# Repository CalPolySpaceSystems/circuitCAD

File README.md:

# Circuit CAD
This repository contains Cal Poly Space Systems' circuit board Design files. 
This includes designed PCBs as well as other resources.
See READMEs in each directory for more information.

# Projects
* UpBoard
* CubeStack
* Flight Recorders
* Peripherals
* Breakouts

# Resources
* Component Libraries
* Design Block/Subassembly Libraries
* CAM jobs for exporting Gerber Files of PCBs

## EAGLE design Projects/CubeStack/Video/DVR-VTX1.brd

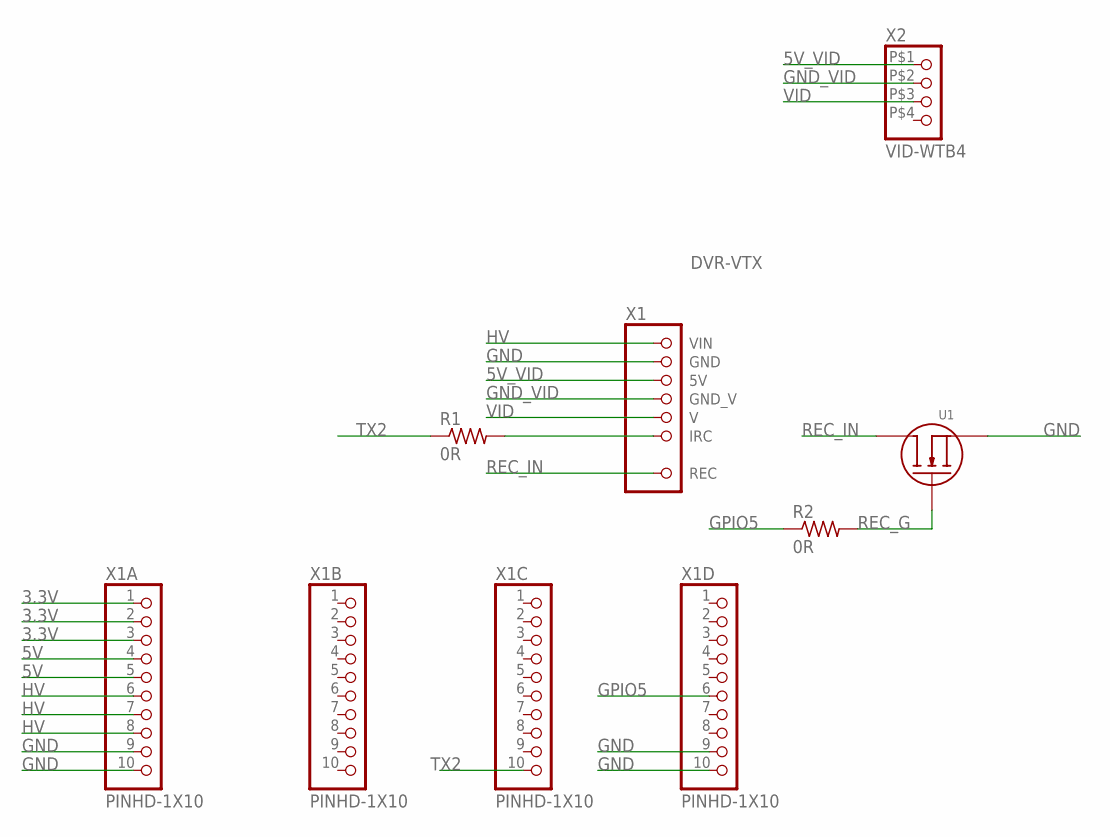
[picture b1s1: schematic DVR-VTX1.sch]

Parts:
R1, R2: 0R; R0603
U1: 2N7002E; NMINI3-R1-B
X1: DVR-VTX
X1A, X1B, X1C, X1D: PINHD-1X10; 1X10-BIG
X2: VID-WTB4; 10114829-10104LF

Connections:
3.3V: X1A.1, X1A.2, X1A.3
5V: X1A.4, X1A.5
5V_VID: X1.P$3 (5V), X2.P$1 (1)
GND: U1.2 (S), X1.P$2 (GND), X1A.9, X1A.10, X1D.9, X1D.10
GND_VID: X1.P$4 (GND_V), X2.P$2 (2)
GPIO5: R2.1, X1D.6
HV: X1.P$1 (VIN), X1A.6, X1A.7, X1A.8
REC_G: R2.2, U1.1 (G)
REC_IN: U1.3 (D), X1.P$7 (REC)
TRAMP: R1.2, X1.P$6 (IRC)
TX2: R1.1, X1C.10
VID: X1.P$5 (V), X2.P$3 (3)

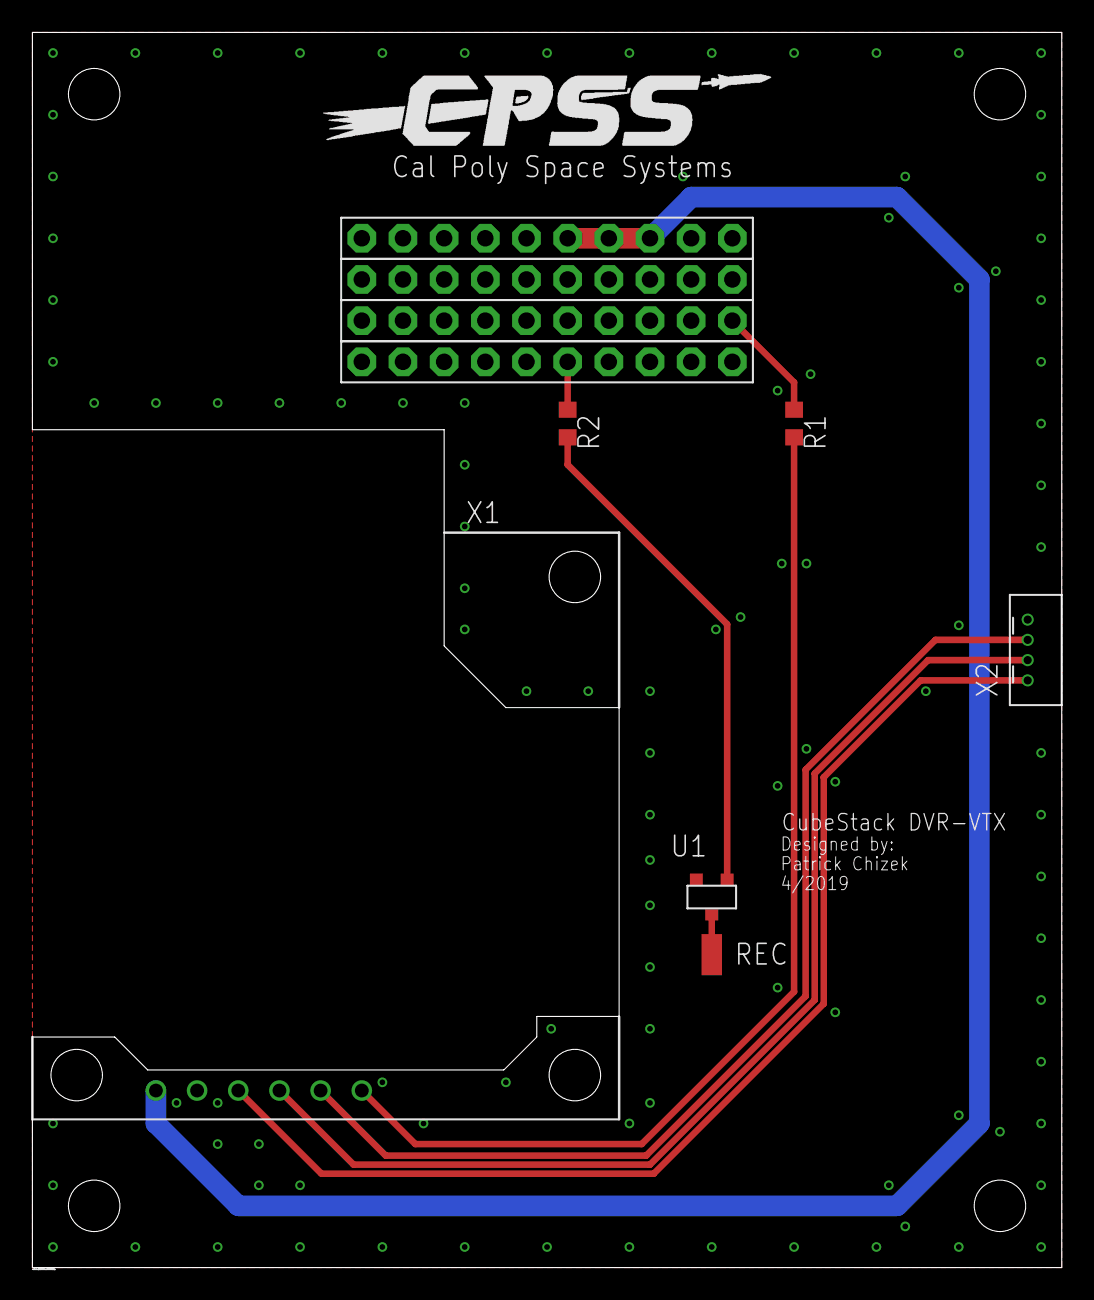
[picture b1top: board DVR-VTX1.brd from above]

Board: 2 copper layers, 63.5 x 76.2 mm, 9 parts (0 on the bottom side), 12 nets.

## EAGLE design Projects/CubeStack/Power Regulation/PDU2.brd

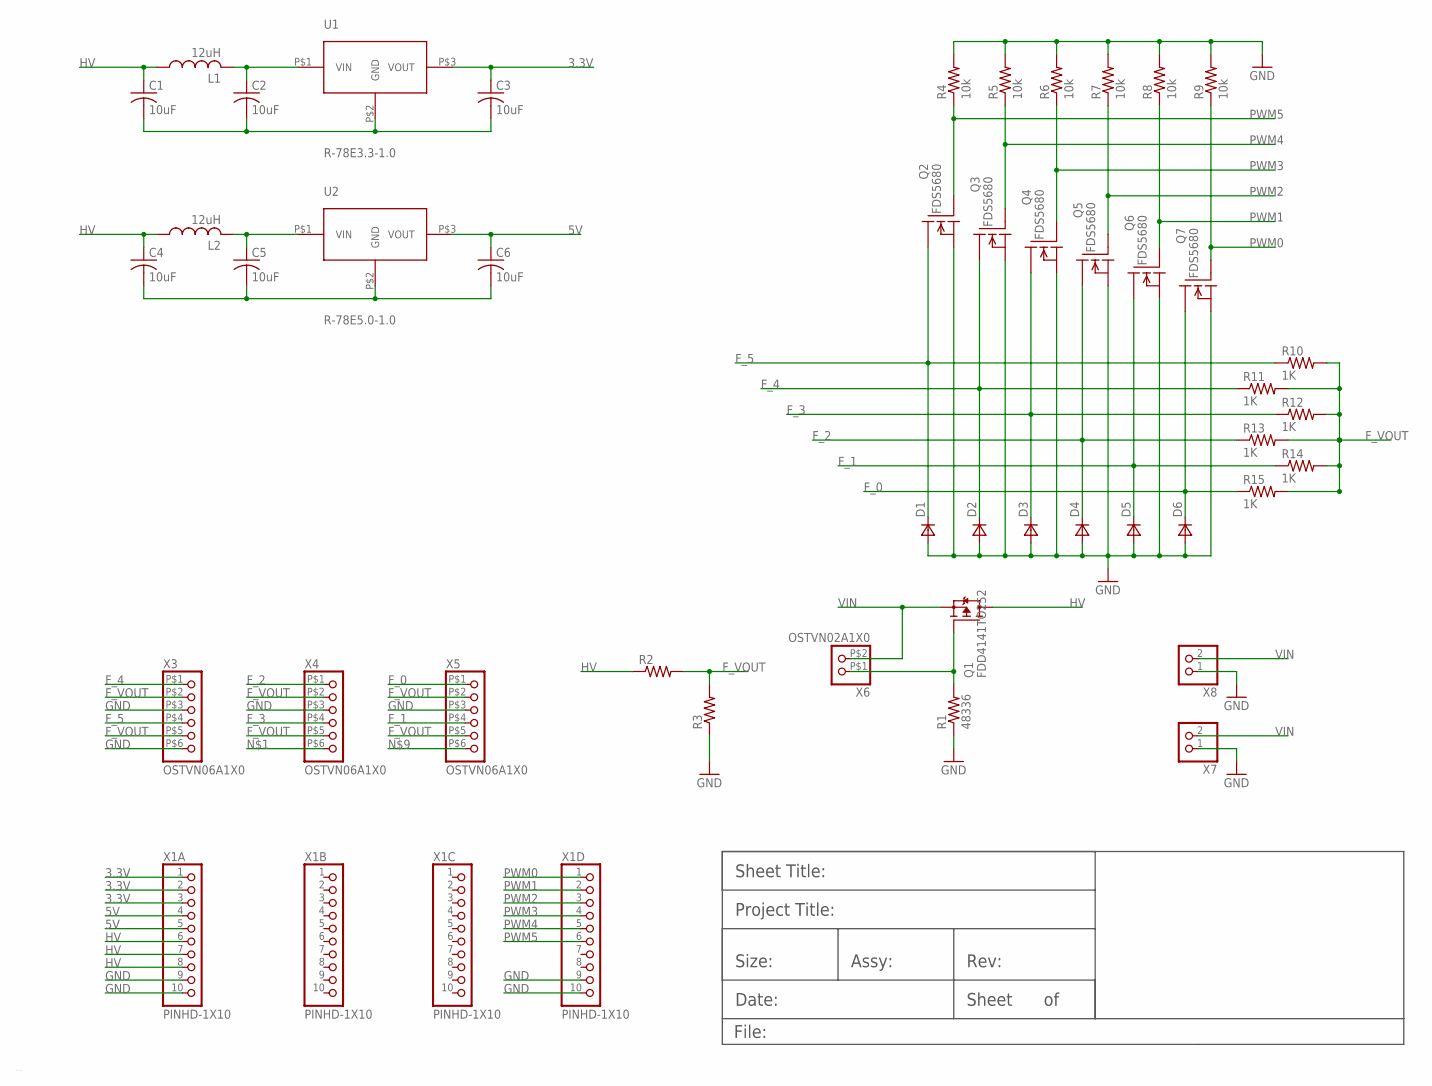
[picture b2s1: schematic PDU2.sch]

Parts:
C1, C2, C3, C4, C5, C6: 10uF; C1206
D1, D2, D3, D4, D5, D6: DSOD323; SOD323
L1, L2: 12uH; L2012C
Q1: FDD4141TO252; TO252
Q2, Q3, Q4, Q5, Q6, Q7: FDS5680; SO-8
R1: 48336; R1206
R2, R3: R-US_R6332; R6332
R4, R5, R6, R7, R8, R9: 10k; R0603
R10, R11, R12, R13, R14, R15: 1K; R0603
U1: R-78E3.3-1.0; R-78E-1.0
U2: R-78E5.0-1.0; R-78E-1.0
X1A, X1B, X1C, X1D: PINHD-1X10; 1X10-BIG
X3, X4, X5: OSTVN06A1X0
X6: OSTVN02A1X0
X7, X8: PINHD-1X2/90; 1X02/90

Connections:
3.3V: C3.1, U1.P$3 (VOUT), X1A.1, X1A.2, X1A.3
5V: C6.1, U2.P$3 (VOUT), X1A.4, X1A.5
EN: Q1.1 (G), R1.2, X6.P$1 (1)
F_0: D6.1 (C), Q7.5 (D), Q7.6 (D), Q7.7 (D), Q7.8 (D), R15.1, X5.P$1 (1)
F_1: D5.1 (C), Q6.5 (D), Q6.6 (D), Q6.7 (D), Q6.8 (D), R14.1, X5.P$4 (4)
F_2: D4.1 (C), Q5.5 (D), Q5.6 (D), Q5.7 (D), Q5.8 (D), R13.1, X4.P$1 (1)
F_3: D3.1 (C), Q4.5 (D), Q4.6 (D), Q4.7 (D), Q4.8 (D), R12.1, X4.P$4 (4)
F_4: D2.1 (C), Q3.5 (D), Q3.6 (D), Q3.7 (D), Q3.8 (D), R11.1, X3.P$1 (1)
F_5: D1.1 (C), Q2.5 (D), Q2.6 (D), Q2.7 (D), Q2.8 (D), R10.1, X3.P$4 (4)
F_VOUT: R2.2, R3.2, R10.2, R11.2, R12.2, R13.2, R14.2, R15.2, X3.P$2 (2), X3.P$5 (5), X4.P$2 (2), X4.P$5 (5), X5.P$2 (2), X5.P$5 (5)
GND: C1.2, C2.2, C3.2, C4.2, C5.2, C6.2, D1.2 (A), D2.2 (A), D3.2 (A), D4.2 (A), D5.2 (A), D6.2 (A), Q2.1 (S), Q2.2 (S), Q2.3 (S), Q3.1 (S), Q3.2 (S), Q3.3 (S), Q4.1 (S), Q4.2 (S), Q4.3 (S), Q5.1 (S), Q5.2 (S), Q5.3 (S), Q6.1 (S), Q6.2 (S), Q6.3 (S), Q7.1 (S), Q7.2 (S), Q7.3 (S), R1.1, R3.1, R4.2, R5.2, R6.2, R7.2, R8.2, R9.2, U1.P$2 (GND), U2.P$2 (GND), X1A.9, X1A.10, X1D.9, X1D.10, X3.P$3 (3), X3.P$6 (6), X4.P$3 (3), X5.P$3 (3), X7.1, X8.1
HV: C1.1, C4.1, L1.1, L2.1, Q1.3 (D), R2.1, X1A.6, X1A.7, X1A.8
unnamed: C2.1, L1.2, U1.P$1 (VIN)
unnamed: C5.1, L2.2, U2.P$1 (VIN)
PWM0: Q7.4 (G), R9.1, X1D.1
PWM1: Q6.4 (G), R8.1, X1D.2
PWM2: Q5.4 (G), R7.1, X1D.3
PWM3: Q4.4 (G), R6.1, X1D.4
PWM4: Q3.4 (G), R5.1, X1D.5
PWM5: Q2.4 (G), R4.1, X1D.6
VIN: Q1.2 (S), X6.P$2 (2), X7.2, X8.2

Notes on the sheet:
C:/Users/patri/Pictures/CPSSLOGO.bmp

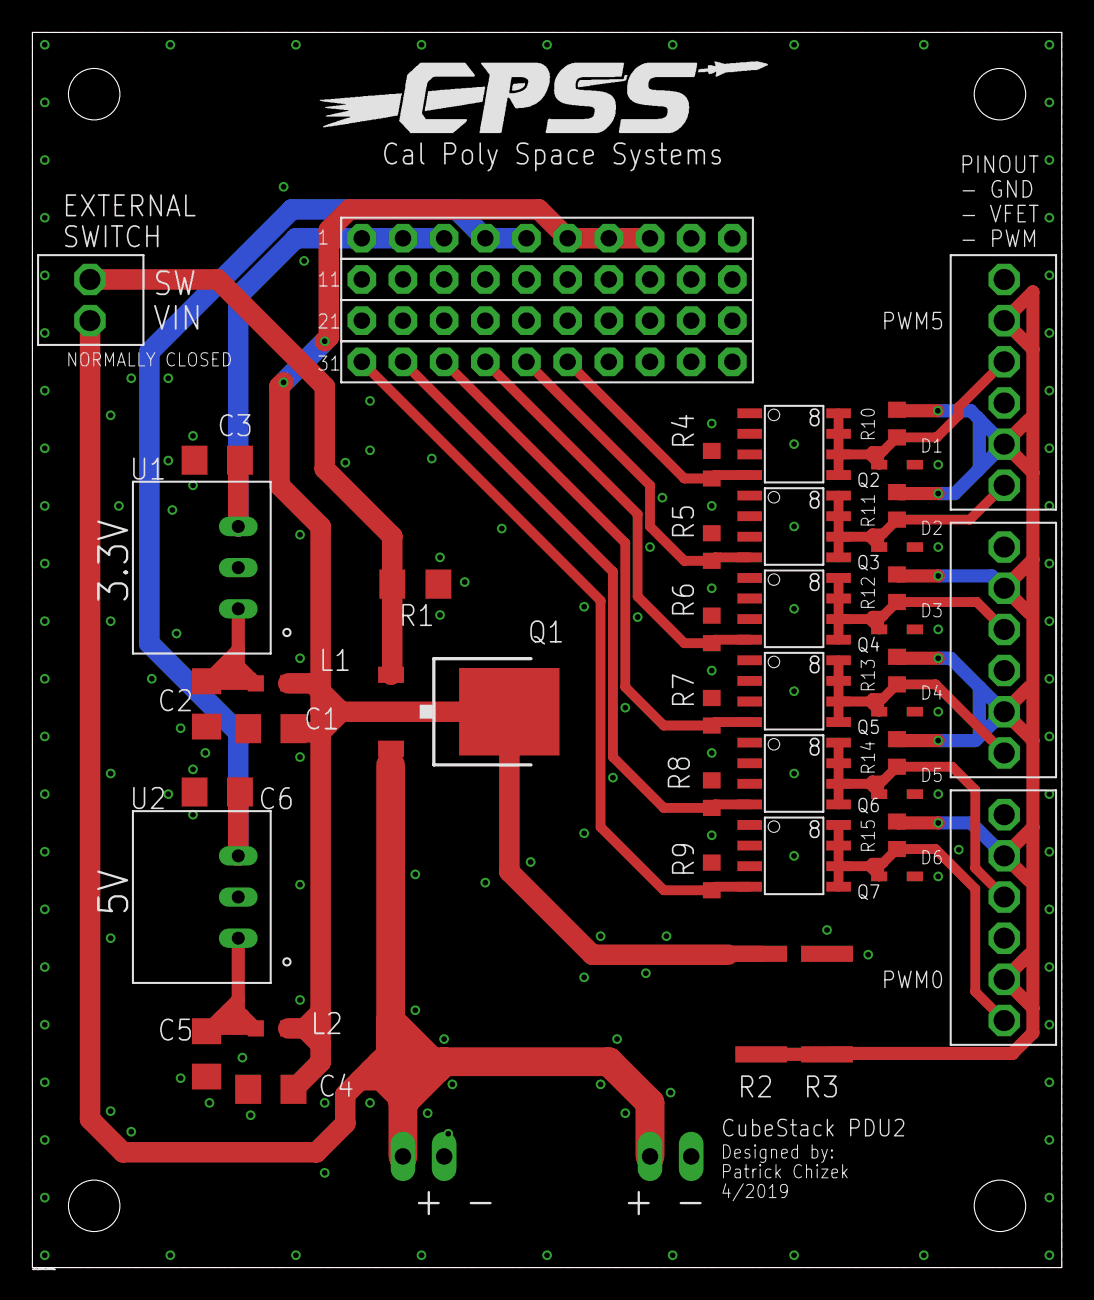
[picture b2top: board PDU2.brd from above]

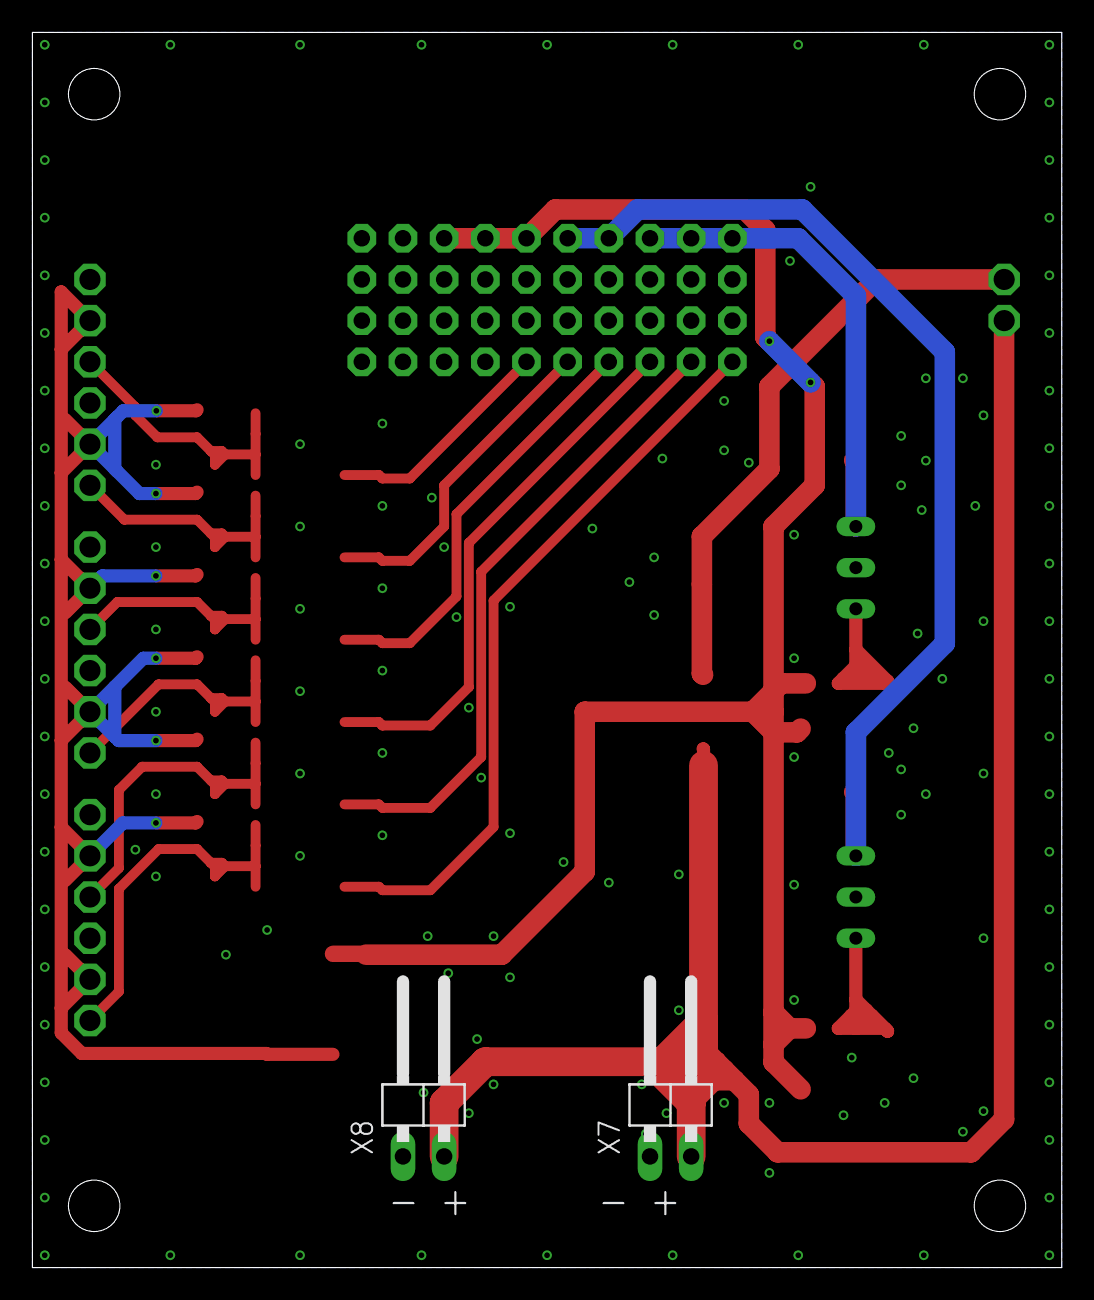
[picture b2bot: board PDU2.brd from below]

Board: 2 copper layers, 63.5 x 76.2 mm, 48 parts (2 on the bottom side), 21 nets.

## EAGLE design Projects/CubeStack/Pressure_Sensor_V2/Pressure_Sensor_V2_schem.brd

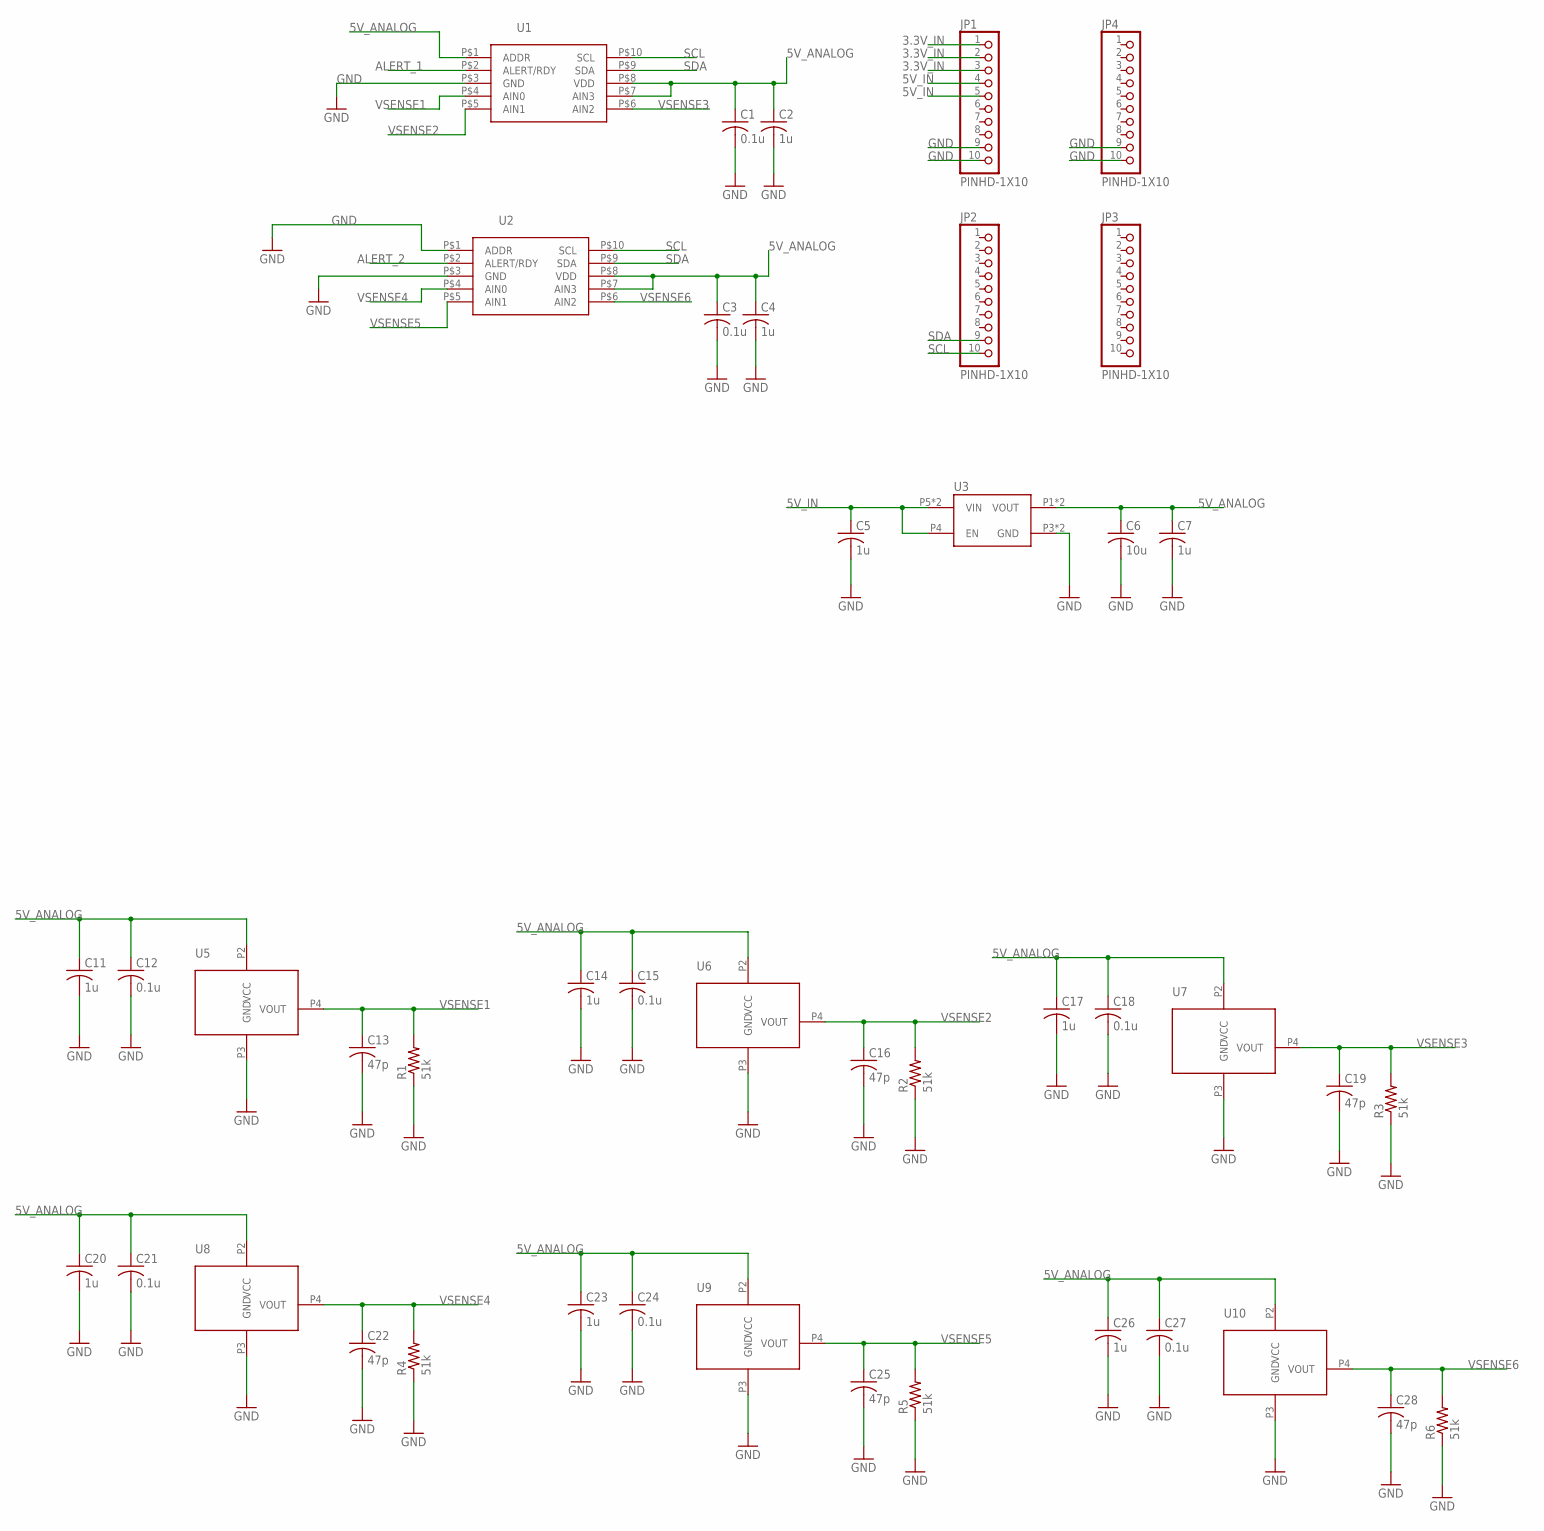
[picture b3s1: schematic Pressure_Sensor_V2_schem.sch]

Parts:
C1, C3, C12, C15, C18, C21, C24, C27: 0.1u; C0805
C2, C4, C5, C7, C11, C14, C17, C20, C23, C26: 1u; C0805
C6: 10u; C0805
C13, C16, C19, C22, C25, C28: 47p; C0805
JP1, JP2, JP3, JP4: PINHD-1X10; 1X10-BIG
R1, R2, R3, R4, R5, R6: 51k; R0805
U1, U2: ADS1115VSSOP; VSSOP-10
U3: ADP196; WLCSP
U5, U6, U7, U8, U9, U10: MPXH6400A; SSOP

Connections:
3.3V_IN: JP1.1, JP1.2, JP1.3
5V_ANALOG: C1.1, C2.1, C3.1, C4.1, C6.1, C7.1, C11.1, C12.1, C14.1, C15.1, C17.1, C18.1, C20.1, C21.1, C23.1, C24.1, C26.1, C27.1, U1.P$1 (ADDR), U1.P$7 (AIN3), U1.P$8 (VDD), U2.P$7 (AIN3), U2.P$8 (VDD), U3.P1 (VOUT), U3.P2 (VOUT), U5.P2 (VCC), U6.P2 (VCC), U7.P2 (VCC), U8.P2 (VCC), U9.P2 (VCC), U10.P2 (VCC)
5V_IN: C5.1, JP1.4, JP1.5, U3.P4 (EN), U3.P5 (VIN), U3.P6 (VIN)
ALERT_1: U1.P$2 (ALERT/RDY)
ALERT_2: U2.P$2 (ALERT/RDY)
GND: C1.2, C2.2, C3.2, C4.2, C5.2, C6.2, C7.2, C11.2, C12.2, C13.2, C14.2, C15.2, C16.2, C17.2, C18.2, C19.2, C20.2, C21.2, C22.2, C23.2, C24.2, C25.2, C26.2, C27.2, C28.2, JP1.9, JP1.10, JP4.9, JP4.10, R1.1, R2.1, R3.1, R4.1, R5.1, R6.1, U1.P$3 (GND), U2.P$1 (ADDR), U2.P$3 (GND), U3.P3 (GND), U3.TH (GND), U5.P3 (GND), U6.P3 (GND), U7.P3 (GND), U8.P3 (GND), U9.P3 (GND), U10.P3 (GND)
SCL: JP2.10, U1.P$10 (SCL), U2.P$10 (SCL)
SDA: JP2.9, U1.P$9 (SDA), U2.P$9 (SDA)
VSENSE1: C13.1, R1.2, U1.P$4 (AIN0), U5.P4 (VOUT)
VSENSE2: C16.1, R2.2, U1.P$5 (AIN1), U6.P4 (VOUT)
VSENSE3: C19.1, R3.2, U1.P$6 (AIN2), U7.P4 (VOUT)
VSENSE4: C22.1, R4.2, U2.P$4 (AIN0), U8.P4 (VOUT)
VSENSE5: C25.1, R5.2, U2.P$5 (AIN1), U9.P4 (VOUT)
VSENSE6: C28.1, R6.2, U2.P$6 (AIN2), U10.P4 (VOUT)

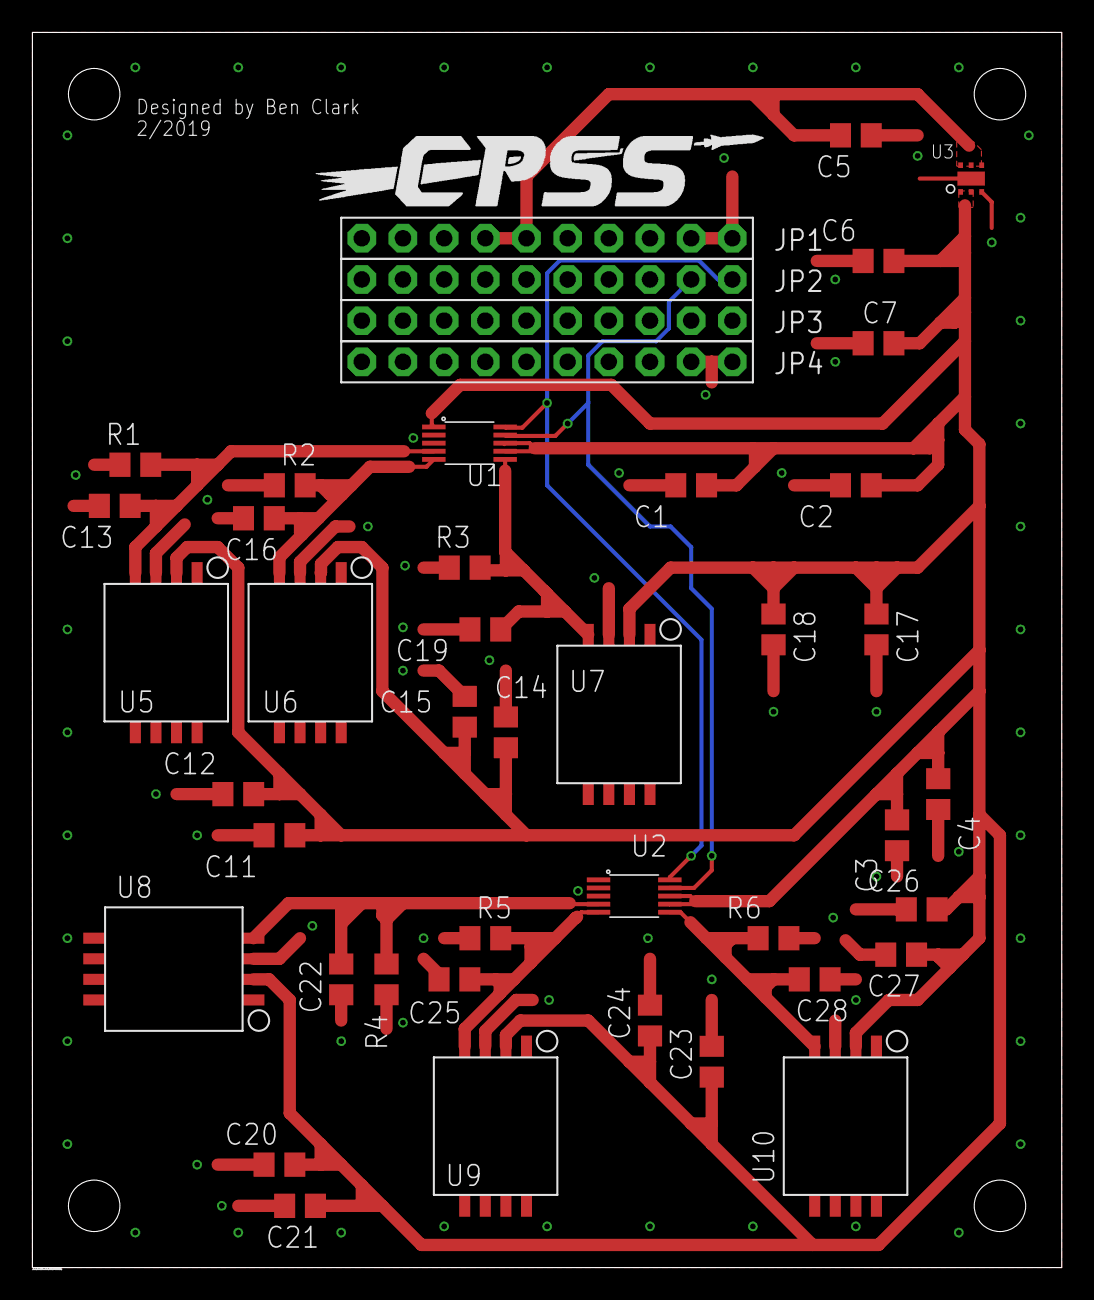
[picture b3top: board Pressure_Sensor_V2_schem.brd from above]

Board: 2 copper layers, 63.5 x 76.2 mm, 44 parts (0 on the bottom side), 12 nets.

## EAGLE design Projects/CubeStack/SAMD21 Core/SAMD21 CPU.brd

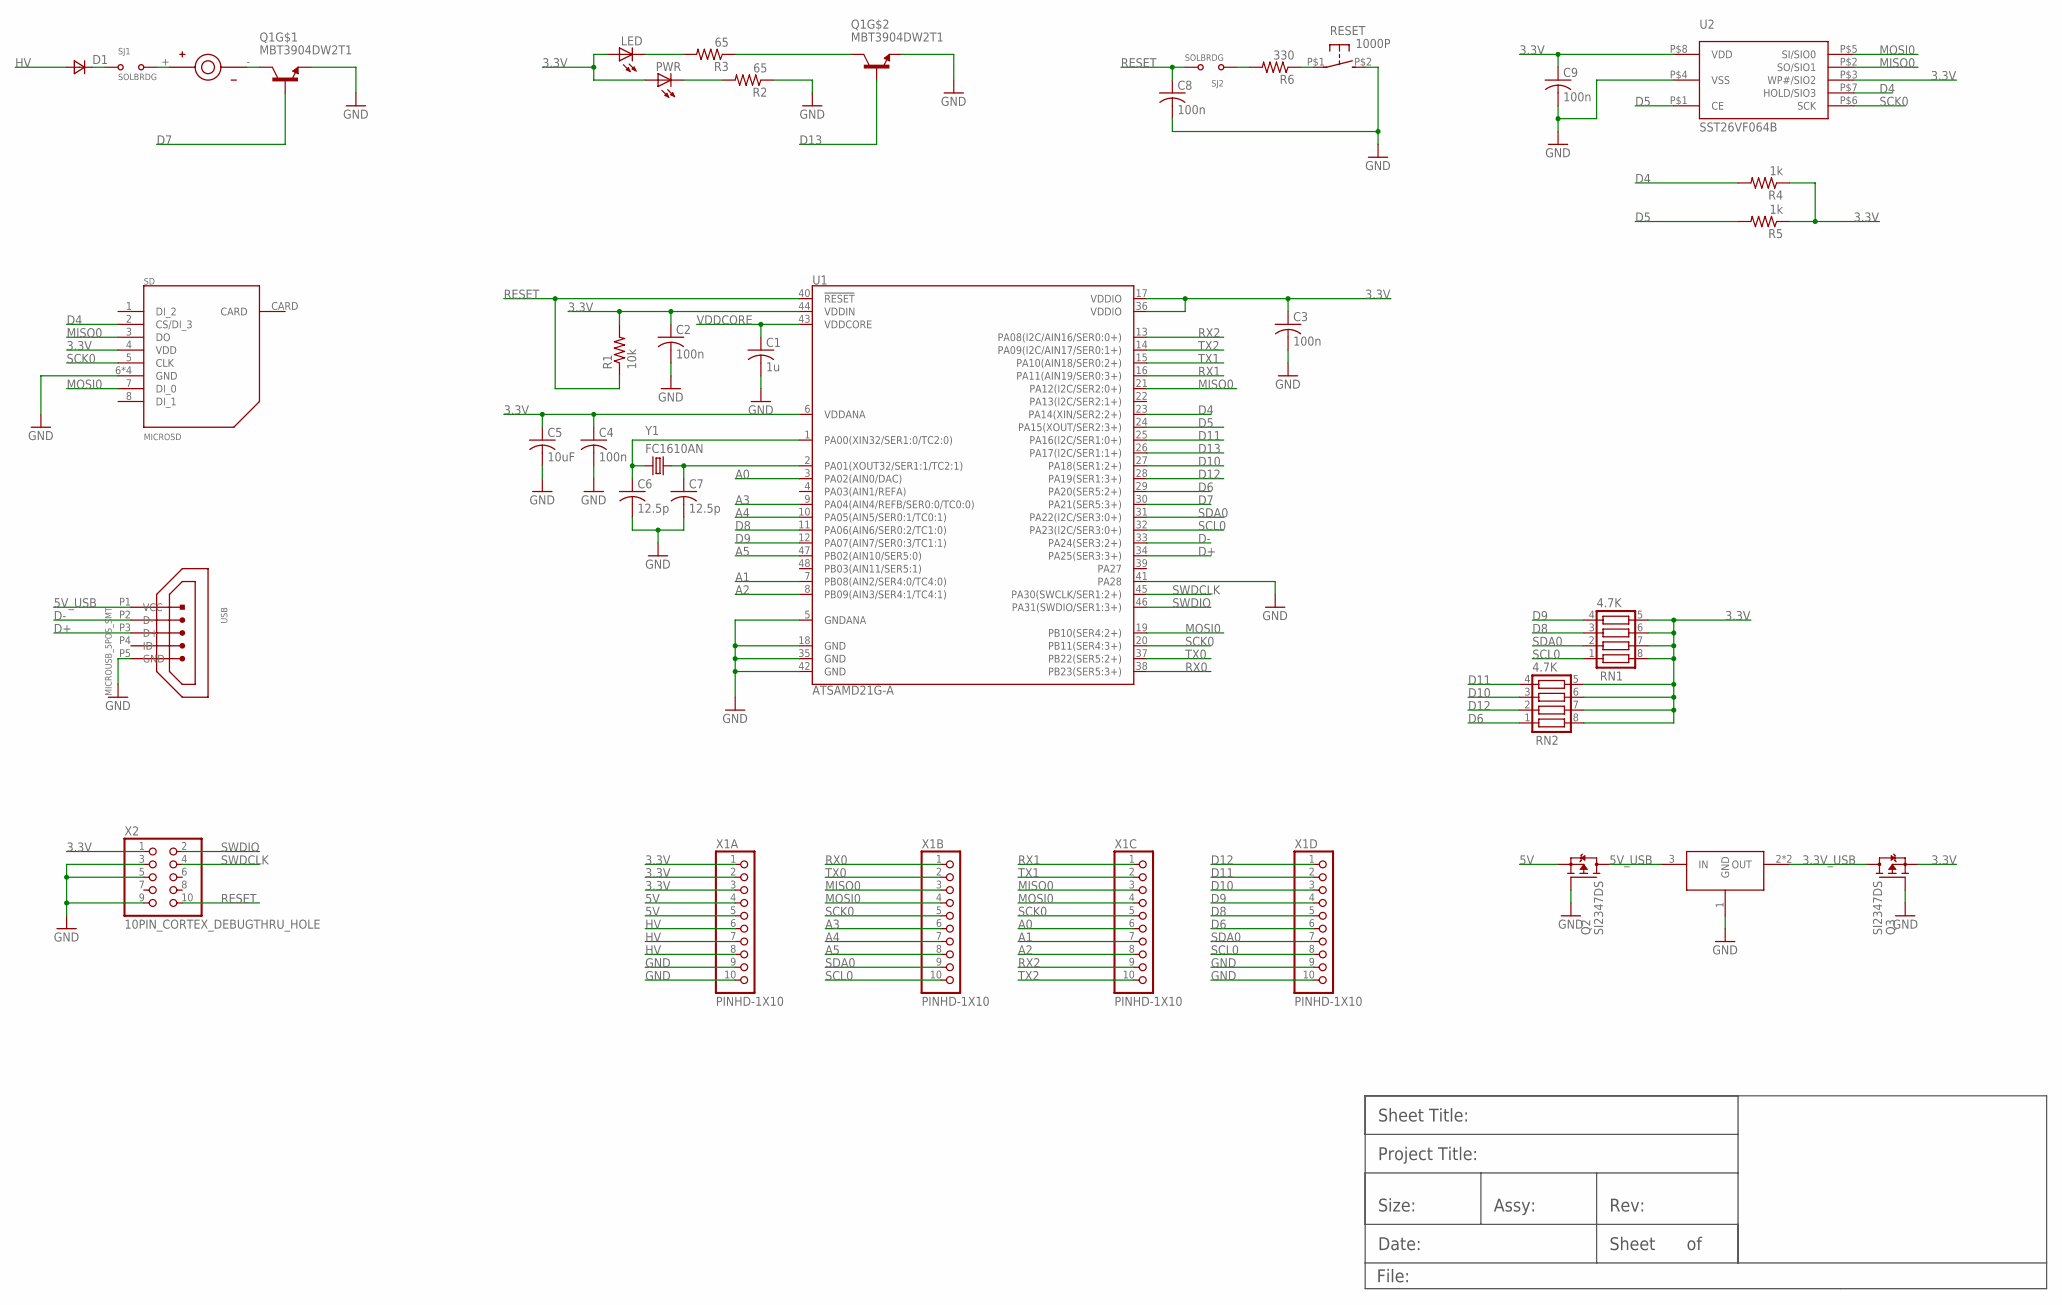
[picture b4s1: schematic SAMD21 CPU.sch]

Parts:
C1: 1u; C0603
C2, C3, C4, C8, C9: 100n; C0603
C5: 10uF; C0603
C6, C7: 12.5p; C0603
D1: DSOD323; SOD323
LED: LEDCHIPLED_0805; CHIPLED_0805
LS1: AI-1440-TWT-24V-2-R; AI-1440-TWT-24-2-R
PWR: LEDCHIPLED_0805; CHIPLED_0805
Q1: MBT3904DW2T1; SOT-363
Q2, Q3: SI2347DS; SOT23
R1: 10k; R0603
R2, R3: 65; R0603
R4, R5: 1k; R0603
R6: 330; R0603
RESET: 1000P; B3U-1000P
RN1, RN2: 4.7K; CTS742C083
SD: MICROSD; CONN_MICROSD
SJ1, SJ2: SOLBRDG
U1: ATSAMD21G-A; TQFP-48
U2: SST26VF064B; SOIJ
U3: AZ1117C; SOT89
USB: MICROUSB_5POS_SMT; RECPT_SMT_R/A
X1A, X1B, X1C, X1D: PINHD-1X10; 1X10-BIG
X2: 10PIN_CORTEX_DEBUGTHRU_HOLE; 2X5-PTH-1.27MM
Y1: FC1610AN; A431L

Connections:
3.3V: C2.1, C3.1, C4.1, C5.1, C9.1, LED.A, PWR.A, Q3.2 (S), R1.2, R4.1, R5.1, RN1.5, RN1.6, RN1.7, RN1.8, RN2.5, RN2.6, RN2.7, RN2.8, SD.4 (VDD), U1.6 (VDDANA), U1.17 (VDDIO), U1.36 (VDDIO), U1.44 (VDDIN), U2.P$3 (WP#/SIO2), U2.P$8 (VDD), X1A.1, X1A.2, X1A.3, X2.1
3.3V_USB: Q3.3 (D), U3.2 (OUT), U3.2@1 (OUT)
5V: Q2.2 (S), X1A.4, X1A.5
5V_USB: Q2.3 (D), U3.3 (IN), USB.P1 (VCC)
A0: U1.3 (PA02(AIN0/DAC)), X1C.6
A1: U1.7 (PB08(AIN2/SER4:0/TC4:0)), X1C.7
A2: U1.8 (PB09(AIN3/SER4:1/TC4:1)), X1C.8
A3: U1.9 (PA04(AIN4/REFB/SER0:0/TC0:0)), X1B.6
A4: U1.10 (PA05(AIN5/SER0:1/TC0:1)), X1B.7
A5: U1.47 (PB02(AIN10/SER5:0)), X1B.8
D4: R4.2, SD.2 (CS/DI_3), U1.23 (PA14(XIN/SER2:2+)), U2.P$7 (HOLD/SIO3)
D5: R5.2, U1.24 (PA15(XOUT/SER2:3+)), U2.P$1 (CE)
D6: RN2.1, U1.29 (PA20(SER5:2+)), X1D.6
D7: Q1.P$2 (B), U1.30 (PA21(SER5:3+))
D8: RN1.3, U1.11 (PA06(AIN6/SER0:2/TC1:0)), X1D.5
D9: RN1.4, U1.12 (PA07(AIN7/SER0:3/TC1:1)), X1D.4
D10: RN2.3, U1.27 (PA18(SER1:2+)), X1D.3
D11: RN2.4, U1.25 (PA16(I2C/SER1:0+)), X1D.2
D12: RN2.2, U1.28 (PA19(SER1:3+)), X1D.1
D13: Q1.P$1 (B), U1.26 (PA17(I2C/SER1:1+))
D+: U1.34 (PA25(SER3:3+)), USB.P3 (D+)
D-: U1.33 (PA24(SER3:2+)), USB.P2 (D-)
GND: C1.2, C2.2, C3.2, C4.2, C5.2, C6.2, C7.2, C8.2, C9.2, Q1.P$3 (E), Q1.P$6 (E), Q2.1 (G), Q3.1 (G), R2.1, RESET.P$2 (S), SD.6 (GND), SD.GND1 (GND), SD.GND2 (GND), SD.GND3 (GND), U1.5 (GNDANA), U1.18 (GND), U1.35 (GND), U1.41 (PA28), U1.42 (GND), U2.P$4 (VSS), U3.1 (GND), USB.P5 (GND), X1A.9, X1A.10, X1D.9, X1D.10, X2.3, X2.5, X2.9
HV: D1.2 (A), X1A.6, X1A.7, X1A.8
LS_D: LS1.-, Q1.P$4 (C)
L_3: LED.C, R3.2
L_3_D: Q1.P$5 (C), R3.1
MISO0: SD.3 (DO), U1.21 (PA12(I2C/SER2:0+)), U2.P$2 (SO/SIO1), X1B.3, X1C.3
MOSI0: SD.7 (DI_0), U1.19 (PB10(SER4:2+)), U2.P$5 (SI/SIO0), X1B.4, X1C.4
unnamed: C6.1, U1.1 (PA00(XIN32/SER1:0/TC2:0)), Y1.P$1 (1)
unnamed: C7.1, U1.2 (PA01(XOUT32/SER1:1/TC2:1)), Y1.P$2 (2)
unnamed: R6.2, SJ2.P$1
unnamed: LS1.+, SJ1.P$2
unnamed: PWR.C, R2.2
unnamed: R6.1, RESET.P$1
unnamed: D1.1 (C), SJ1.P$1
RESET: C8.1, R1.1, SJ2.P$2, U1.40 (!RESET!), X2.10
RX0: U1.38 (PB23(SER5:3+)), X1B.1
RX1: U1.16 (PA11(AIN19/SER0:3+)), X1C.1
RX2: U1.13 (PA08(I2C/AIN16/SER0:0+)), X1C.9
SCK0: SD.5 (CLK), U1.20 (PB11(SER4:3+)), U2.P$6 (SCK), X1B.5, X1C.5
SCL0: RN1.1, U1.32 (PA23(I2C/SER3:0+)), X1B.10, X1D.8
SDA0: RN1.2, U1.31 (PA22(I2C/SER3:0+)), X1B.9, X1D.7
SWDCLK: U1.45 (PA30(SWCLK/SER1:2+)), X2.4
SWDIO: U1.46 (PA31(SWDIO/SER1:3+)), X2.2
TX0: U1.37 (PB22(SER5:2+)), X1B.2
TX1: U1.15 (PA10(AIN18/SER0:2+)), X1C.2
TX2: U1.14 (PA09(I2C/AIN17/SER0:1+)), X1C.10
VDDCORE: C1.1, U1.43 (VDDCORE)

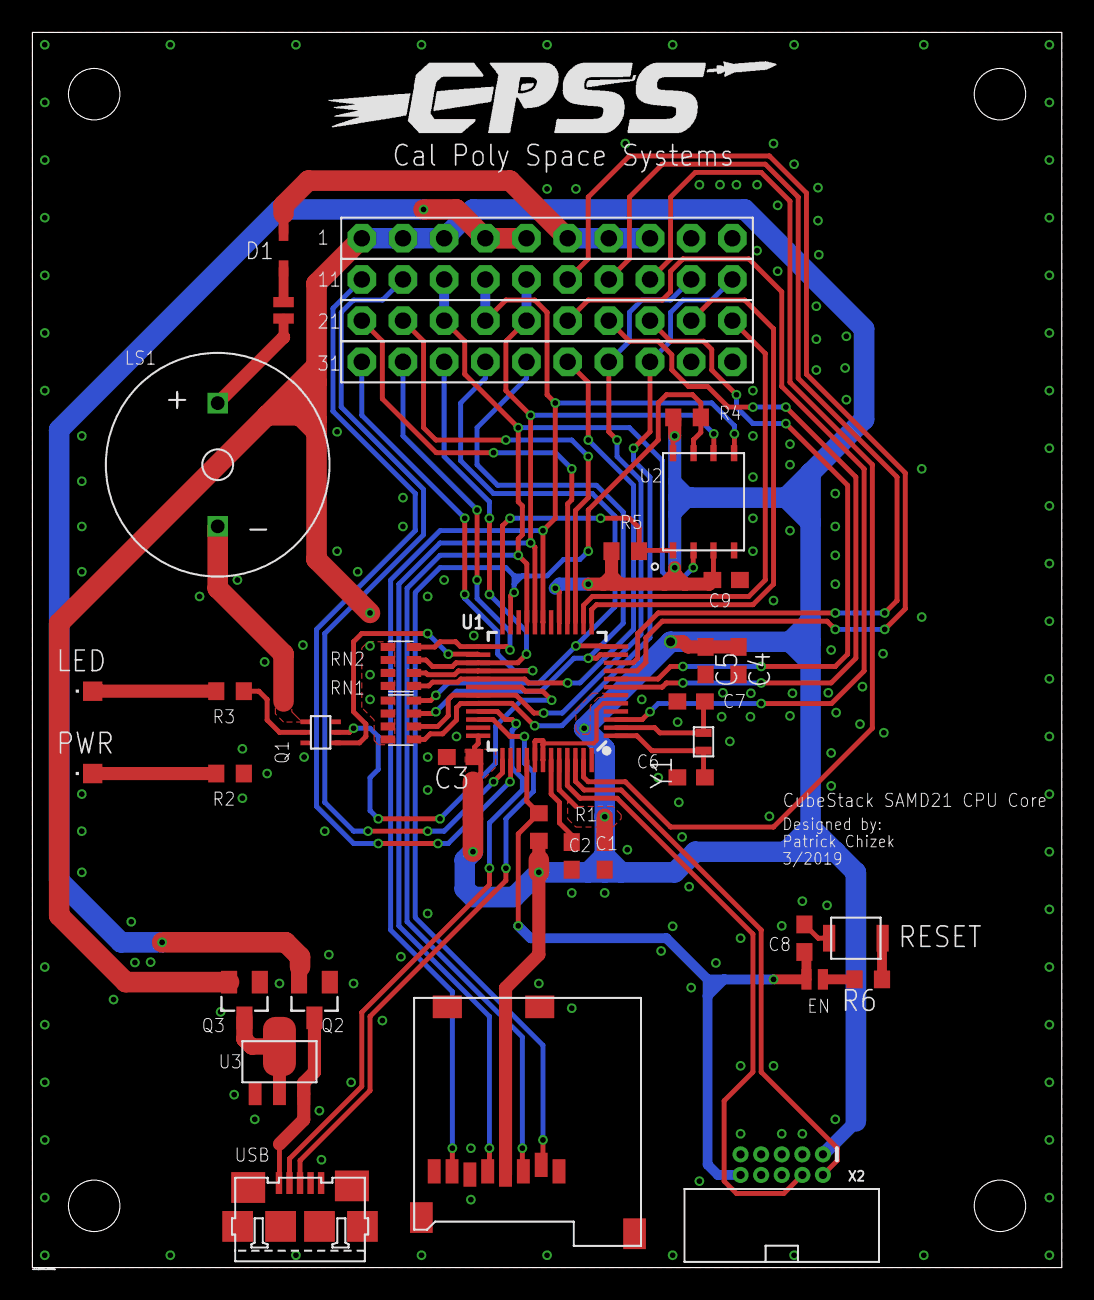
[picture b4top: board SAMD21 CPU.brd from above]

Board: 2 copper layers, 63.5 x 76.2 mm, 38 parts (0 on the bottom side), 49 nets.

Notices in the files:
parts and their libraries:
SparkFun-RF: Licensing: Creative Commons ShareAlike 4.0 International - https://creativecommons.org/licenses/by-sa/4.0
